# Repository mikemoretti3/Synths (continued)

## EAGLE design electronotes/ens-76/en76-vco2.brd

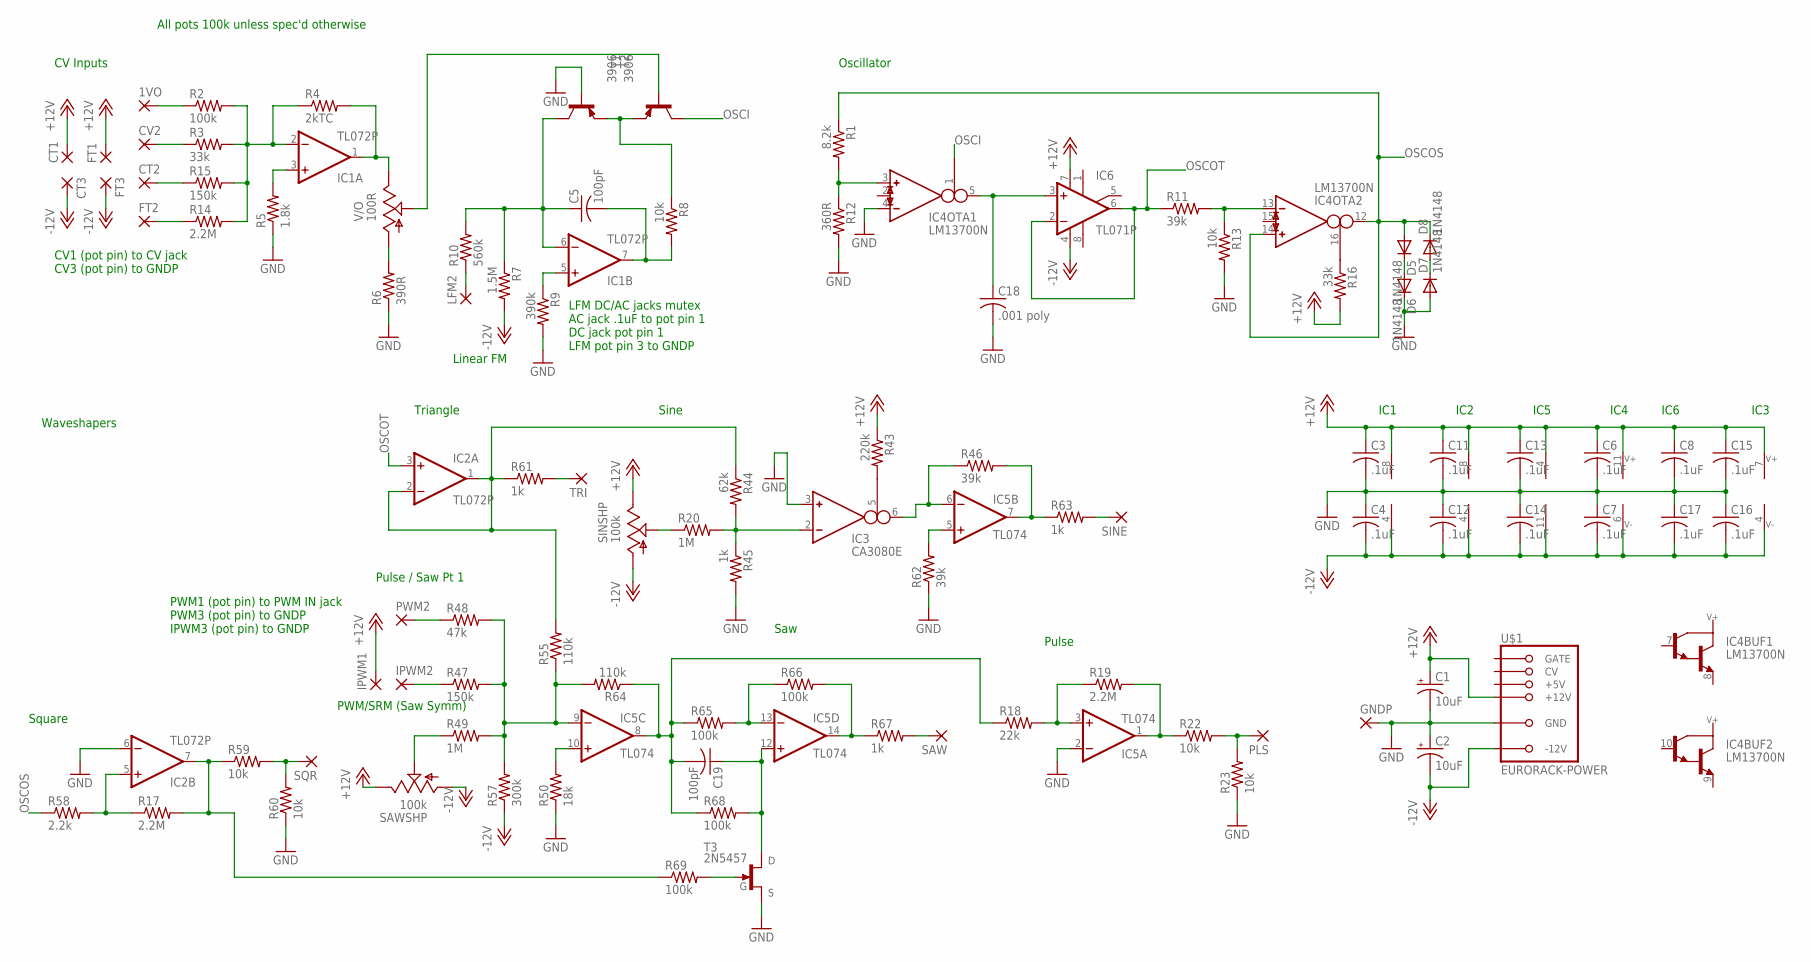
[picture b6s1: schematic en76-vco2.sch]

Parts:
1VO: 2,54/1,0
C1, C2: 10uF; E2-5
C3, C4, C6, C7, C8, C11, C12, C13, C14, C15, C16, C17: .1uF; C050-025X075
C5, C19: 100pF; C050-025X075
C18: .001 poly; C050-025X075
CT1, CT2, CT3: 2,54/1,0
CV2: 2,54/1,0
D5, D6, D7, D8: 1N4148; DO35-7
FT1, FT2, FT3: 2,54/1,0
GNDP: 2,54/1,0
IC1, IC2: TL072P; DIL08
IC3: CA3080E; DIL08
IC4: LM13700N; DIL16
IC5: TL074; DIL14
IC6: TL071P; DIL08
IPWM1, IPWM2: 2,54/1,0
LFM2: 2,54/1,0
PLS: 2,54/1,0
PWM2: 2,54/1,0
R1: 8.2k; 0207/10
R2, R65, R66, R68, R69: 100k; 0207/10
R3, R16: 33k; 0207/10
R4: 2kTC; 0207/10
R5: 1.8k; 0207/10
R6: 390R; 0207/10
R7: 1.5M; 0207/10
R8, R13, R22, R23, R59, R60: 10k; 0207/10
R9: 390k; 0207/10
R10: 560k; 0207/10
R11, R46, R62: 39k; 0207/10
R12: 360R; 0207/10
R14, R17, R19: 2.2M; 0207/10
R15, R47: 150k; 0207/10
R18: 22k; 0207/10
R20, R49: 1M; 0207/10
R43: 220k; 0207/10
R44: 62k; 0207/10
R45, R61, R63, R67: 1k; 0207/10
R48: 47k; 0207/10
R50: 18k; 0207/10
R55, R64: 110k; 0207/10
R57: 300k; 0207/10
R58: 2.2k; 0207/10
SAW: 2,54/1,0
SAWSHP: 100k; RJ9W
SINE: 2,54/1,0
SINSHP: 100k; RJ9W
SQR: 2,54/1,0
T1, T2: 3906; TO92-EBC
T3: 2N5457; TO-92
TRI: 2,54/1,0
U$1: EURORACK-POWER; PINSHRD_PTH_2X8
V/O: 100R; RJ9W

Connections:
+12V: C1.+, C3.1, C6.1, C8.1, C11.1, C13.1, C15.1, CT1.1, FT1.1, IC1.8 (V+), IC2.8 (V+), IC3.7, IC4.11 (7), IC5.4 (V+), IC6.7 (V+), IPWM1.1, R16.2, R43.1, SAWSHP.E, SINSHP.E, U$1.+12V@1 (+12V), U$1.+12V@2 (+12V)
-12V: C2.-, C4.2, C7.2, C12.2, C14.2, C16.2, C17.2, CT3.1, FT3.1, IC1.4 (V-), IC2.4 (V-), IC3.4, IC4.6 (4), IC5.11 (V-), IC6.4 (V-), R7.2, R57.1, SAWSHP.A, SINSHP.A, U$1.-12V@1 (-12V), U$1.-12V@2 (-12V)
GND: C1.-, C2.+, C3.2, C4.1, C6.2, C7.1, C8.2, C11.2, C12.1, C13.2, C14.1, C15.2, C16.1, C17.1, C18.2, D6.C, D7.A, GNDP.1, IC2.6 (-IN), IC3.3 (IN_P), IC4.4 (IN_N), IC5.2 (-IN), R5.1, R6.1, R9.2, R12.2, R13.2, R23.1, R45.2, R50.1, R60.1, R62.1, T2.B, T3.2 (S), U$1.GND@1 (GND), U$1.GND@2 (GND), U$1.GND@3 (GND), U$1.GND@4 (GND), U$1.GND@5 (GND), U$1.GND@6 (GND)
unnamed: CT2.1, R15.1
unnamed: CV2.1, R3.1
unnamed: 1VO.1, R2.1
unnamed: T1.B, V/O.S
unnamed: IC1.3 (+IN), R5.2
unnamed: IC1.2 (-IN), R2.2, R3.2, R4.1, R14.2, R15.2
unnamed: IC1.1 (OUT), R4.2, V/O.E
unnamed: R6.2, V/O.A
unnamed: C5.1, IC1.6 (-IN), R7.1, R10.2, T2.C
unnamed: R8.1, T1.E, T2.E
unnamed: C5.2, IC1.7 (OUT), R8.2
unnamed: FT2.1, R14.1
unnamed: LFM2.1, R10.1
unnamed: IC1.5 (+IN), R9.1
unnamed: IC2.5 (+IN), R17.1, R58.2
unnamed: C18.1, IC4.5 (OUT), IC6.3 (+IN)
unnamed: IPWM2.1, R47.1
unnamed: R59.2, R60.2, SQR.1
unnamed: IC5.9 (-IN), R47.2, R48.2, R49.2, R55.1, R57.2, R64.2
unnamed: IC4.3 (IN_P), R1.2, R12.1
unnamed: IC4.13 (IN_N), R11.2, R13.1
unnamed: R20.1, SINSHP.S
unnamed: IC5.3 (+IN), R18.2, R19.1
unnamed: IC5.1 (OUT), R19.2, R22.1
unnamed: IC3.5 (I_BIAS), R43.2
unnamed: IC3.6 (OUT), IC5.6 (-IN), R46.1
unnamed: IC3.2 (IN_N), R20.2, R44.2, R45.1
unnamed: PWM2.1, R48.1
unnamed: R49.1, SAWSHP.S
unnamed: IC5.10 (+IN), R50.2
unnamed: C19.2, IC5.8 (OUT), R18.1, R64.1, R65.1, R68.1
unnamed: IC4.16 (I_BIAS), R16.1
unnamed: IC5.13 (-IN), R65.2, R66.1
unnamed: R61.2, TRI.1
unnamed: D5.C, D6.A
unnamed: D7.C, D8.A
unnamed: IC5.7 (OUT), R46.2, R63.1
unnamed: IC5.5 (+IN), R62.2
unnamed: R63.2, SINE.1
unnamed: R67.2, SAW.1
unnamed: IC5.14 (OUT), R66.2, R67.1
unnamed: C19.1, IC5.12 (+IN), R68.2, T3.1 (D)
unnamed: R69.2, T3.3 (G)
unnamed: PLS.1, R22.2, R23.2
OSCI: IC4.1 (I_BIAS), T1.C
OSCOS: D5.A, D8.C, IC4.12 (OUT), IC4.14 (IN_P), R1.1, R58.1
OSCOT: IC2.3 (+IN), IC6.2 (-IN), IC6.6 (OUT), R11.1
SQX: IC2.7 (OUT), R17.2, R59.1, R69.1
TRIANGLE: IC2.1 (OUT), IC2.2 (-IN), R44.1, R55.2, R61.1

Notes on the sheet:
CV1 (pot pin) to CV jack CV3 (pot pin) to GNDP
LFM DC/AC jacks mutex AC jack .1uF to pot pin 1 DC jack pot pin 1 LFM pot pin 3 to GNDP
All pots 100k unless spec'd otherwise
PWM1 (pot pin) to PWM IN jack PWM3 (pot pin) to GNDP IPWM3 (pot pin) to GNDP
CV Inputs
Oscillator
Waveshapers
Triangle
Saw
Square
Sine
Pulse / Saw Pt 1
Linear FM
IC6
IC1
IC2
IC5
IC4
IC3
Pulse
PWM/SRM (Saw Symm)

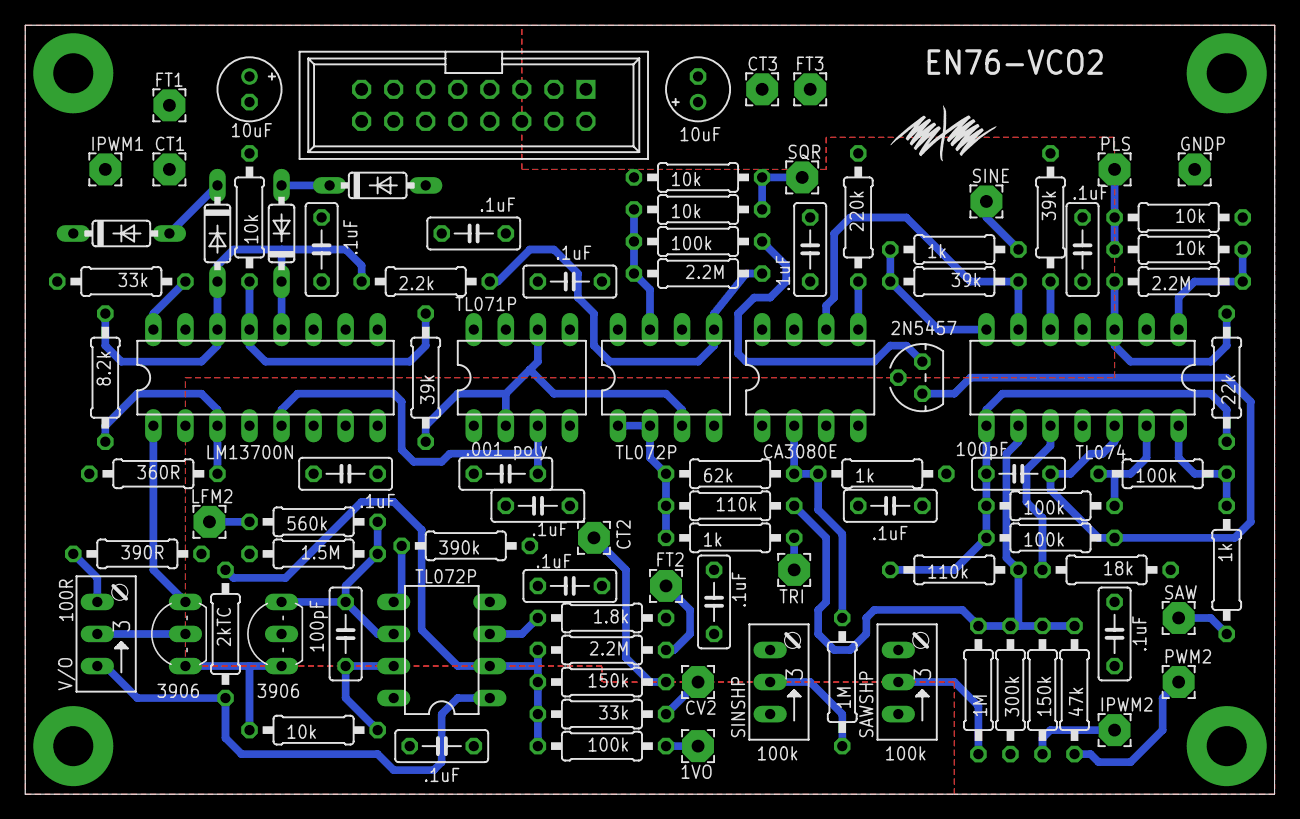
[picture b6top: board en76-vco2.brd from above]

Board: 2 copper layers, 99.1 x 61.0 mm, 96 parts (0 on the bottom side), 52 nets.

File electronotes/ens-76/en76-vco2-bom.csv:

"Part";"Value";"Device";"Package";"Description";"";
"1VO";"";"2,54/1,0";"2,54/1,0";"THROUGH-HOLE PAD";"";
"C1";"10uF";"CPOL-USE2-5";"E2-5";"POLARIZED CAPACITOR, American symbol";"";
"C2";"10uF";"CPOL-USE2-5";"E2-5";"POLARIZED CAPACITOR, American symbol";"";
"C3";".1uF";"C-US050-025X075";"C050-025X075";"CAPACITOR, American symbol";"";
"C4";".1uF";"C-US050-025X075";"C050-025X075";"CAPACITOR, American symbol";"";
"C5";"100pF";"C-US050-025X075";"C050-025X075";"CAPACITOR, American symbol";"";
"C6";".1uF";"C-US050-025X075";"C050-025X075";"CAPACITOR, American symbol";"";
"C7";".1uF";"C-US050-025X075";"C050-025X075";"CAPACITOR, American symbol";"";
"C8";".1uF";"C-US050-025X075";"C050-025X075";"CAPACITOR, American symbol";"";
"C11";".1uF";"C-US050-025X075";"C050-025X075";"CAPACITOR, American symbol";"";
"C12";".1uF";"C-US050-025X075";"C050-025X075";"CAPACITOR, American symbol";"";
"C13";".1uF";"C-US050-025X075";"C050-025X075";"CAPACITOR, American symbol";"";
"C14";".1uF";"C-US050-025X075";"C050-025X075";"CAPACITOR, American symbol";"";
"C15";".1uF";"C-US050-025X075";"C050-025X075";"CAPACITOR, American symbol";"";
"C16";".1uF";"C-US050-025X075";"C050-025X075";"CAPACITOR, American symbol";"";
"C17";".1uF";"C-US050-025X075";"C050-025X075";"CAPACITOR, American symbol";"";
"C18";".001 poly";"C-US050-025X075";"C050-025X075";"CAPACITOR, American symbol";"";
"C19";"100pF";"C-US050-025X075";"C050-025X075";"CAPACITOR, American symbol";"";
"CT1";"";"2,54/1,0";"2,54/1,0";"THROUGH-HOLE PAD";"";
"CT2";"";"2,54/1,0";"2,54/1,0";"THROUGH-HOLE PAD";"";
"CT3";"";"2,54/1,0";"2,54/1,0";"THROUGH-HOLE PAD";"";
"CV2";"";"2,54/1,0";"2,54/1,0";"THROUGH-HOLE PAD";"";
"D5";"1N4148";"1N4148DO35-7";"DO35-7";"DIODE";"";
"D6";"1N4148";"1N4148DO35-7";"DO35-7";"DIODE";"";
"D7";"1N4148";"1N4148DO35-7";"DO35-7";"DIODE";"";
"D8";"1N4148";"1N4148DO35-7";"DO35-7";"DIODE";"";
"FT1";"";"2,54/1,0";"2,54/1,0";"THROUGH-HOLE PAD";"";
"FT2";"";"2,54/1,0";"2,54/1,0";"THROUGH-HOLE PAD";"";
"FT3";"";"2,54/1,0";"2,54/1,0";"THROUGH-HOLE PAD";"";
"GNDP";"";"2,54/1,0";"2,54/1,0";"THROUGH-HOLE PAD";"";
"IC1";"TL072P";"TL072P";"DIL08";"OP AMP";"";
"IC2";"TL072P";"TL072P";"DIL08";"OP AMP";"";
"IC3";"CA3080E";"CA3080E";"DIL08";"OTA";"";
"IC4";"LM13700N";"LM13700N";"DIL16";"Dual OTA with buffers";"";
"IC5";"TL074";"TL074-TOPP";"DIL14";"OP AMP";"";
"IC6";"TL071P";"TL071P";"DIL08";"OP AMP";"";
"IPWM1";"";"2,54/1,0";"2,54/1,0";"THROUGH-HOLE PAD";"";
"IPWM2";"";"2,54/1,0";"2,54/1,0";"THROUGH-HOLE PAD";"";
"LFM2";"";"2,54/1,0";"2,54/1,0";"THROUGH-HOLE PAD";"";
"PLS";"";"2,54/1,0";"2,54/1,0";"THROUGH-HOLE PAD";"";
"PWM2";"";"2,54/1,0";"2,54/1,0";"THROUGH-HOLE PAD";"";
"R1";"8.2k";"R-US_0207/10";"0207/10";"RESISTOR, American symbol";"";
"R2";"100k";"R-US_0207/10";"0207/10";"RESISTOR, American symbol";"";
"R3";"33k";"R-US_0207/10";"0207/10";"RESISTOR, American symbol";"";
"R4";"2kTC";"R-US_0207/10";"0207/10";"RESISTOR, American symbol";"";
"R5";"1.8k";"R-US_0207/10";"0207/10";"RESISTOR, American symbol";"";
"R6";"390R";"R-US_0207/10";"0207/10";"RESISTOR, American symbol";"";
"R7";"1.5M";"R-US_0207/10";"0207/10";"RESISTOR, American symbol";"";
"R8";"10k";"R-US_0207/10";"0207/10";"RESISTOR, American symbol";"";
"R9";"390k";"R-US_0207/10";"0207/10";"RESISTOR, American symbol";"";
"R10";"560k";"R-US_0207/10";"0207/10";"RESISTOR, American symbol";"";
"R11";"39k";"R-US_0207/10";"0207/10";"RESISTOR, American symbol";"";
"R12";"360R";"R-US_0207/10";"0207/10";"RESISTOR, American symbol";"";
"R13";"10k";"R-US_0207/10";"0207/10";"RESISTOR, American symbol";"";
"R14";"2.2M";"R-US_0207/10";"0207/10";"RESISTOR, American symbol";"";
"R15";"150k";"R-US_0207/10";"0207/10";"RESISTOR, American symbol";"";
"R16";"33k";"R-US_0207/10";"0207/10";"RESISTOR, American symbol";"";
"R17";"2.2M";"R-US_0207/10";"0207/10";"RESISTOR, American symbol";"";
"R18";"22k";"R-US_0207/10";"0207/10";"RESISTOR, American symbol";"";
"R19";"2.2M";"R-US_0207/10";"0207/10";"RESISTOR, American symbol";"";
"R20";"1M";"R-US_0207/10";"0207/10";"RESISTOR, American symbol";"";
"R22";"10k";"R-US_0207/10";"0207/10";"RESISTOR, American symbol";"";
"R23";"10k";"R-US_0207/10";"0207/10";"RESISTOR, American symbol";"";
"R43";"220k";"R-US_0207/10";"0207/10";"RESISTOR, American symbol";"";
"R44";"62k";"R-US_0207/10";"0207/10";"RESISTOR, American symbol";"";
"R45";"1k";"R-US_0207/10";"0207/10";"RESISTOR, American symbol";"";
"R46";"39k";"R-US_0207/10";"0207/10";"RESISTOR, American symbol";"";
"R47";"150k";"R-US_0207/10";"0207/10";"RESISTOR, American symbol";"";
"R48";"47k";"R-US_0207/10";"0207/10";"RESISTOR, American symbol";"";
"R49";"1M";"R-US_0207/10";"0207/10";"RESISTOR, American symbol";"";
"R50";"18k";"R-US_0207/10";"0207/10";"RESISTOR, American symbol";"";
"R55";"110k";"R-US_0207/10";"0207/10";"RESISTOR, American symbol";"";
"R57";"300k";"R-US_0207/10";"0207/10";"RESISTOR, American symbol";"";
"R58";"2.2k";"R-US_0207/10";"0207/10";"RESISTOR, American symbol";"";
"R59";"10k";"R-US_0207/10";"0207/10";"RESISTOR, American symbol";"";
"R60";"10k";"R-US_0207/10";"0207/10";"RESISTOR, American symbol";"";
"R61";"1k";"R-US_0207/10";"0207/10";"RESISTOR, American symbol";"";
"R62";"39k";"R-US_0207/10";"0207/10";"RESISTOR, American symbol";"";
"R63";"1k";"R-US_0207/10";"0207/10";"RESISTOR, American symbol";"";
"R64";"110k";"R-US_0207/10";"0207/10";"RESISTOR, American symbol";"";
"R65";"100k";"R-US_0207/10";"0207/10";"RESISTOR, American symbol";"";
"R66";"100k";"R-US_0207/10";"0207/10";"RESISTOR, American symbol";"";
"R67";"1k";"R-US_0207/10";"0207/10";"RESISTOR, American symbol";"";
"R68";"100k";"R-US_0207/10";"0207/10";"RESISTOR, American symbol";"";
"R69";"100k";"R-US_0207/10";"0207/10";"RESISTOR, American symbol";"";
"SAW";"";"2,54/1,0";"2,54/1,0";"THROUGH-HOLE PAD";"";
"SAWSHP";"100k";"TRIM_US-RJ9W";"RJ9W";"POTENTIOMETER";"";
"SINE";"";"2,54/1,0";"2,54/1,0";"THROUGH-HOLE PAD";"";
"SINSHP";"100k";"TRIM_US-RJ9W";"RJ9W";"POTENTIOMETER";"";
"SQR";"";"2,54/1,0";"2,54/1,0";"THROUGH-HOLE PAD";"";
"T1";"3906";"2N3906-PNP-TO92-EBC";"TO92-EBC";"PNP Transistror";"";
"T2";"3906";"2N3906-PNP-TO92-EBC";"TO92-EBC";"PNP Transistror";"";
"T3";"2N5457";"2N5457";"TO-92";"2N54xx N-channel JFET";"";
"TRI";"";"2,54/1,0";"2,54/1,0";"THROUGH-HOLE PAD";"";
"U$1";"EURORACK-POWER";"EURORACK-POWER";"PINSHRD_PTH_2X8";"";"";
"V/O";"100R";"TRIM_US-RJ9W";"RJ9W";"POTENTIOMETER";"";

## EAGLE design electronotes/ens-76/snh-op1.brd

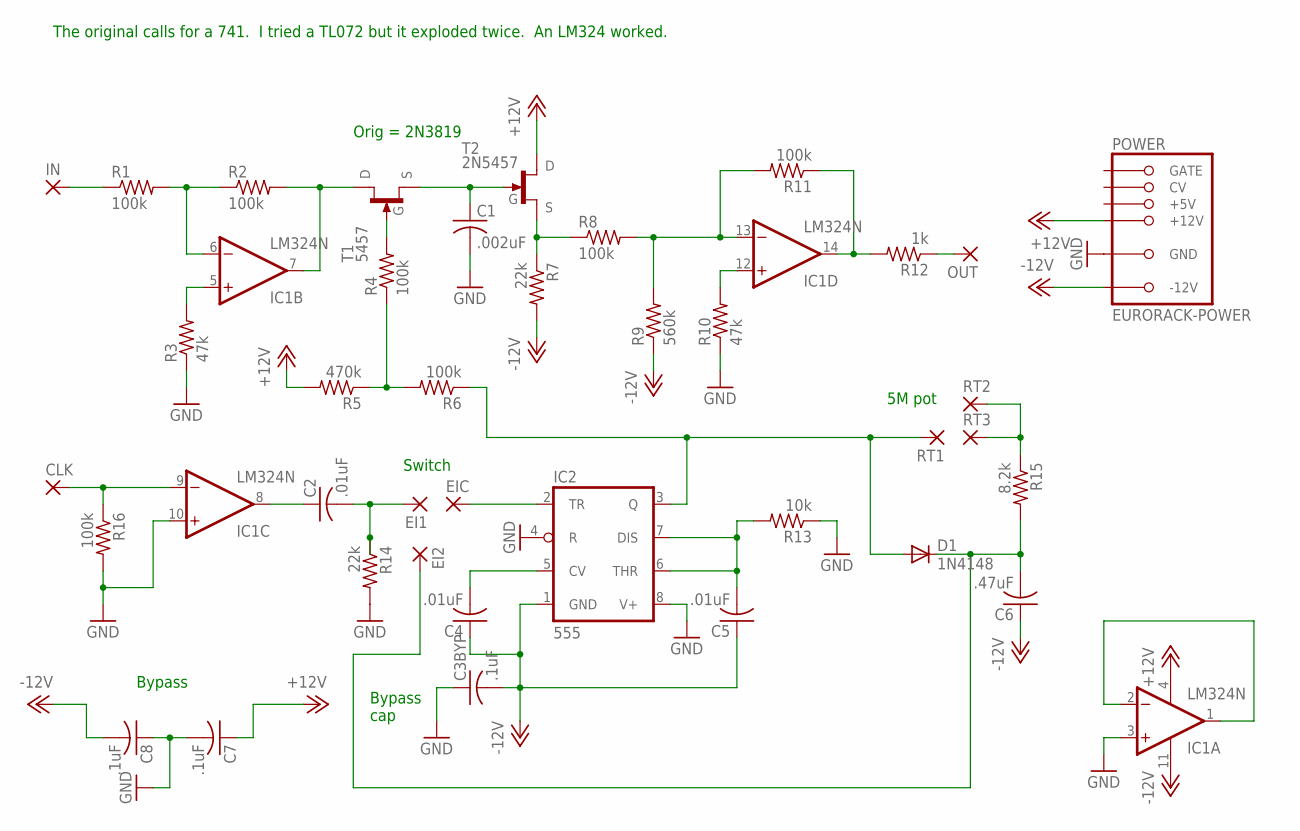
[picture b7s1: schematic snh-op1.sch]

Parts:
C1: .002uF; C050-025X075
C2, C4, C5: .01uF; C050-025X075
C3BYP, C7, C8: .1uF; C050-025X075
C6: .47uF; C050-025X075
CLK: 2,54/1,0
D1: 1N4148; DO35-7
EI1, EI2: 2,54/1,0
EIC: 2,54/1,0
IC1: LM324N; DIL14
IC2: 555; DIL08
IN: 2,54/1,0
OUT: 2,54/1,0
POWER: EURORACK-POWER; PINSHRD_PTH_2X8
R1, R2, R4, R6, R8, R11, R16: 100k; 0207/10
R3, R10: 47k; 0207/10
R5: 470k; 0207/10
R7, R14: 22k; 0207/10
R9: 560k; 0207/10
R12: 1k; 0207/10
R13: 10k; 0207/10
R15: 8.2k; 0207/10
RT1, RT2, RT3: 2,54/1,0
T1: 5457; TO-92
T2: 2N5457; TO-92

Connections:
+12V: C7.1, IC1.4 (V+), POWER.+12V@1 (+12V), POWER.+12V@2 (+12V), R5.2, T2.1 (D)
-12V: C3BYP.2, C4.1, C5.1, C6.1, C8.2, IC1.11 (V-), IC2.1 (GND), POWER.-12V@1 (-12V), POWER.-12V@2 (-12V), R7.2, R9.1
GND: C1.2, C3BYP.1, C7.2, C8.1, IC1.3 (+IN), IC1.10 (+IN), IC2.4 (R), IC2.8 (V+), POWER.GND@1 (GND), POWER.GND@2 (GND), POWER.GND@3 (GND), POWER.GND@4 (GND), POWER.GND@5 (GND), POWER.GND@6 (GND), R3.1, R10.1, R13.1, R14.2, R16.2
unnamed: IN.1, R1.1
unnamed: IC1.6 (-IN), R1.2, R2.1
unnamed: IC1.5 (+IN), R3.2
unnamed: IC1.7 (OUT), R2.2, T1.1 (D)
unnamed: R4.2, T1.3 (G)
unnamed: R4.1, R5.1, R6.2
unnamed: C1.1, T1.2 (S), T2.3 (G)
unnamed: R7.1, R8.1, T2.2 (S)
unnamed: IC1.13 (-IN), R8.2, R9.2, R11.2
unnamed: IC1.12 (+IN), R10.2
unnamed: IC1.14 (OUT), R11.1, R12.2
unnamed: OUT.1, R12.1
unnamed: CLK.1, IC1.9 (-IN), R16.1
unnamed: C4.2, IC2.5 (CV)
unnamed: C2.1, IC1.8 (OUT)
unnamed: C2.2, EI1.1, R14.1
unnamed: C5.2, IC2.6 (THR), IC2.7 (DIS), R13.2
unnamed: C6.2, D1.C, EI2.1, R15.2
unnamed: IC1.1 (OUT), IC1.2 (-IN)
unnamed: EIC.1, IC2.2 (TR)
unnamed: R15.1, RT2.1, RT3.1
unnamed: D1.A, IC2.3 (Q), R6.1, RT1.1

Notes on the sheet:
The original calls for a 741. I tried a TL072 but it exploded twice. An LM324 worked.
Bypass cap
5M pot
Switch
Orig = 2N3819
Bypass

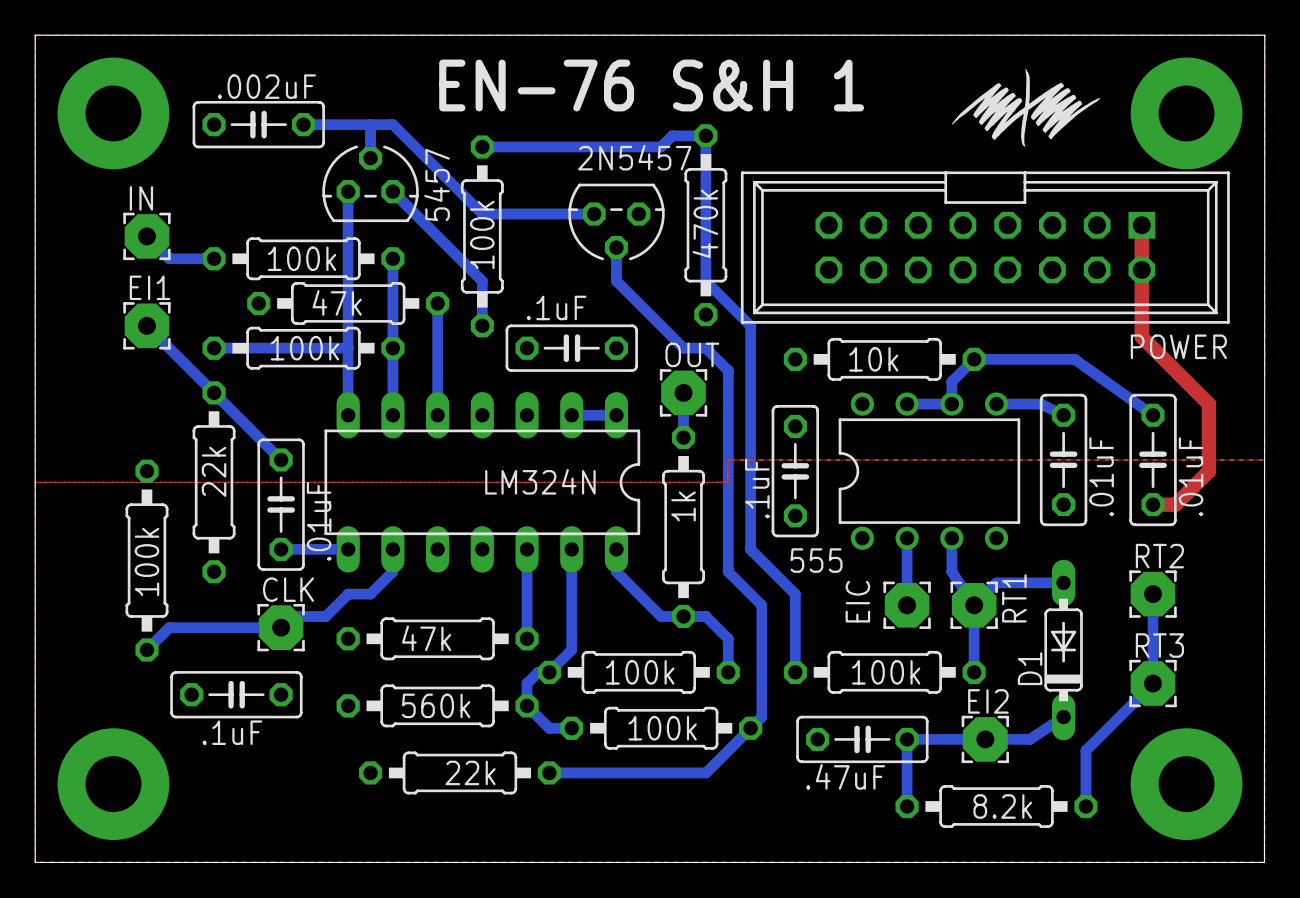
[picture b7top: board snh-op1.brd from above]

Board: 2 copper layers, 69.8 x 47.0 mm, 39 parts (0 on the bottom side), 25 nets.

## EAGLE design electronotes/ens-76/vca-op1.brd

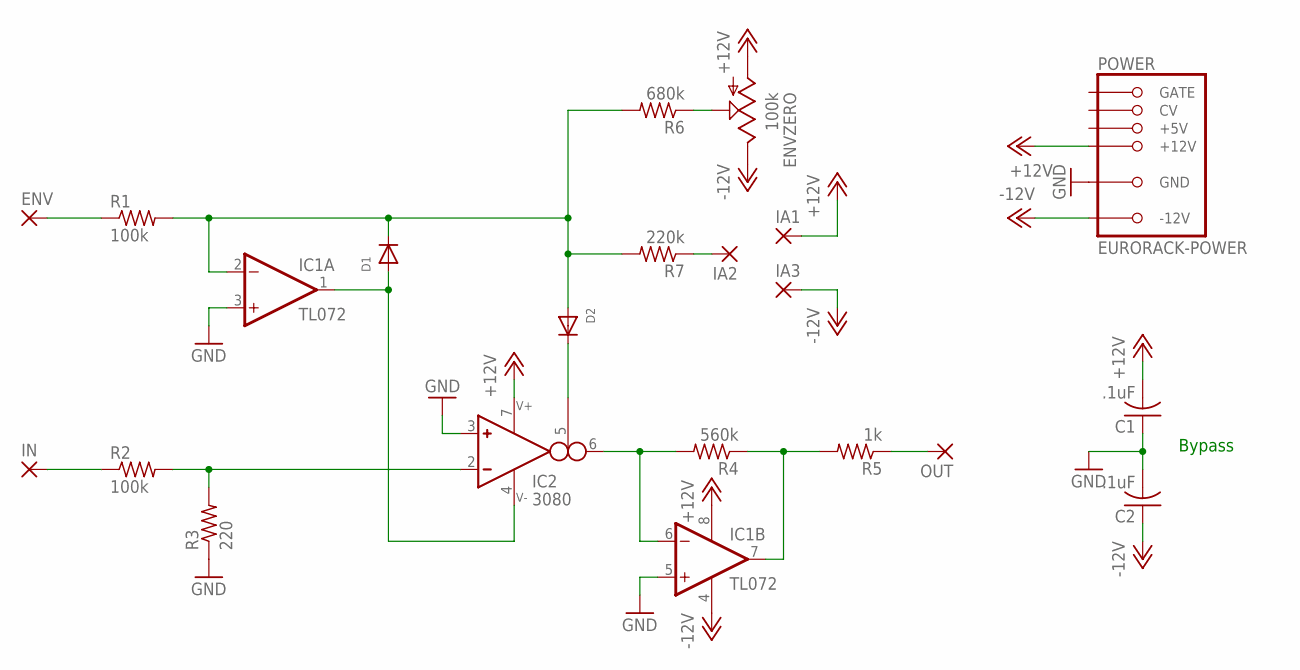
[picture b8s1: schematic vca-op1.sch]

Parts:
C1, C2: .1uF; C050-025X075
D1, D2: DIODEDO-1N4148; DO-1N4148
ENV: 2,54/1,0
ENVZERO: 100k; RJ9W
IA1, IA2, IA3: 2,54/1,0
IC1: TL072; DIL08
IC2: 3080; DIL08
IN: 2,54/1,0
OUT: 2,54/1,0
POWER: EURORACK-POWER; PINSHRD_PTH_2X8
R1, R2: 100k; 0207/10
R3: 220; 0207/10
R4: 560k; 0207/10
R5: 1k; 0207/10
R6: 680k; 0207/10
R7: 220k; 0207/10

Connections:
+12V: C1.2, ENVZERO.A, IA1.1, IC1.8 (V+), IC2.7 (V+), POWER.+12V@1 (+12V), POWER.+12V@2 (+12V)
-12V: C2.1, ENVZERO.E, IA3.1, IC1.4 (V-), POWER.-12V@1 (-12V), POWER.-12V@2 (-12V)
GND: C1.1, C2.2, IC1.3 (+IN), IC1.5 (+IN), IC2.3 (IN_P), POWER.GND@1 (GND), POWER.GND@2 (GND), POWER.GND@3 (GND), POWER.GND@4 (GND), POWER.GND@5 (GND), POWER.GND@6 (GND), R3.1
unnamed: D1.C, D2.A, IC1.2 (-IN), R1.2, R6.2, R7.2
unnamed: ENV.1, R1.1
unnamed: D2.C, IC2.5 (I_BIAS)
unnamed: IN.1, R2.1
unnamed: IC2.2 (IN_N), R2.2, R3.2
unnamed: ENVZERO.S, R6.1
unnamed: IC1.6 (-IN), IC2.6 (OUT), R4.2
unnamed: IC1.7 (OUT), R4.1, R5.2
unnamed: OUT.1, R5.1
unnamed: IA2.1, R7.1
V-: D1.A, IC1.1 (OUT), IC2.4 (V-)

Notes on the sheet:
Bypass

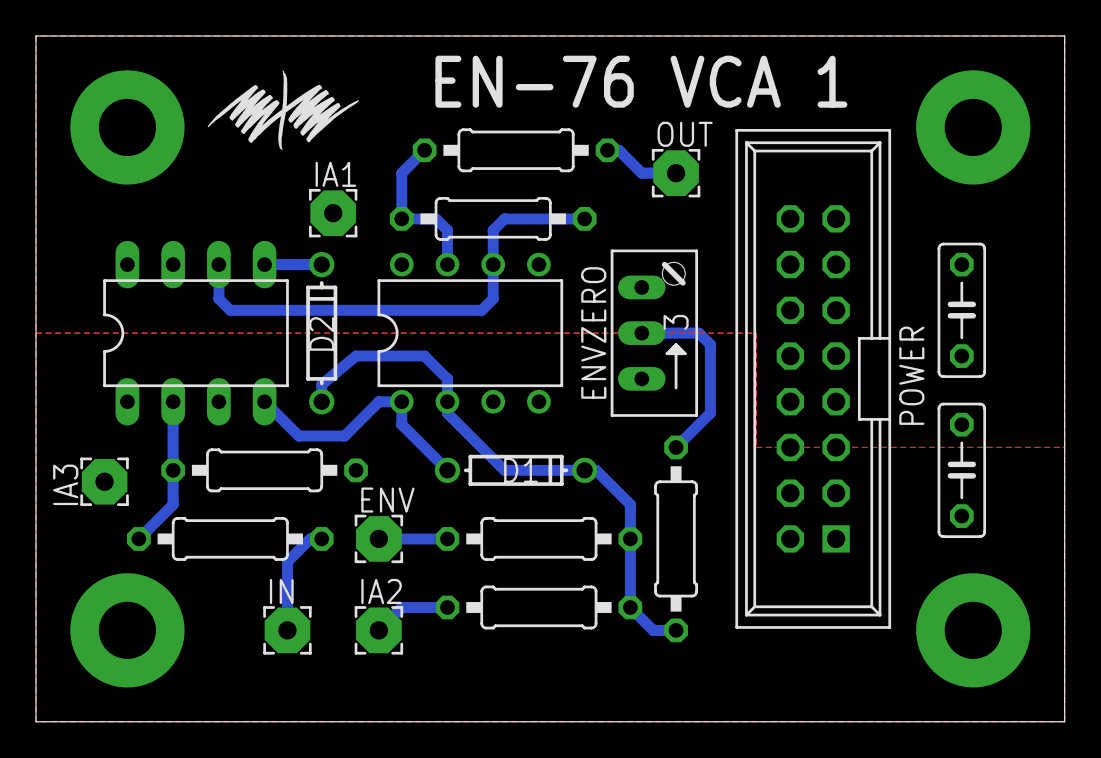
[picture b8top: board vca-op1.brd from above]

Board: 2 copper layers, 57.1 x 38.1 mm, 21 parts (0 on the bottom side), 14 nets.
